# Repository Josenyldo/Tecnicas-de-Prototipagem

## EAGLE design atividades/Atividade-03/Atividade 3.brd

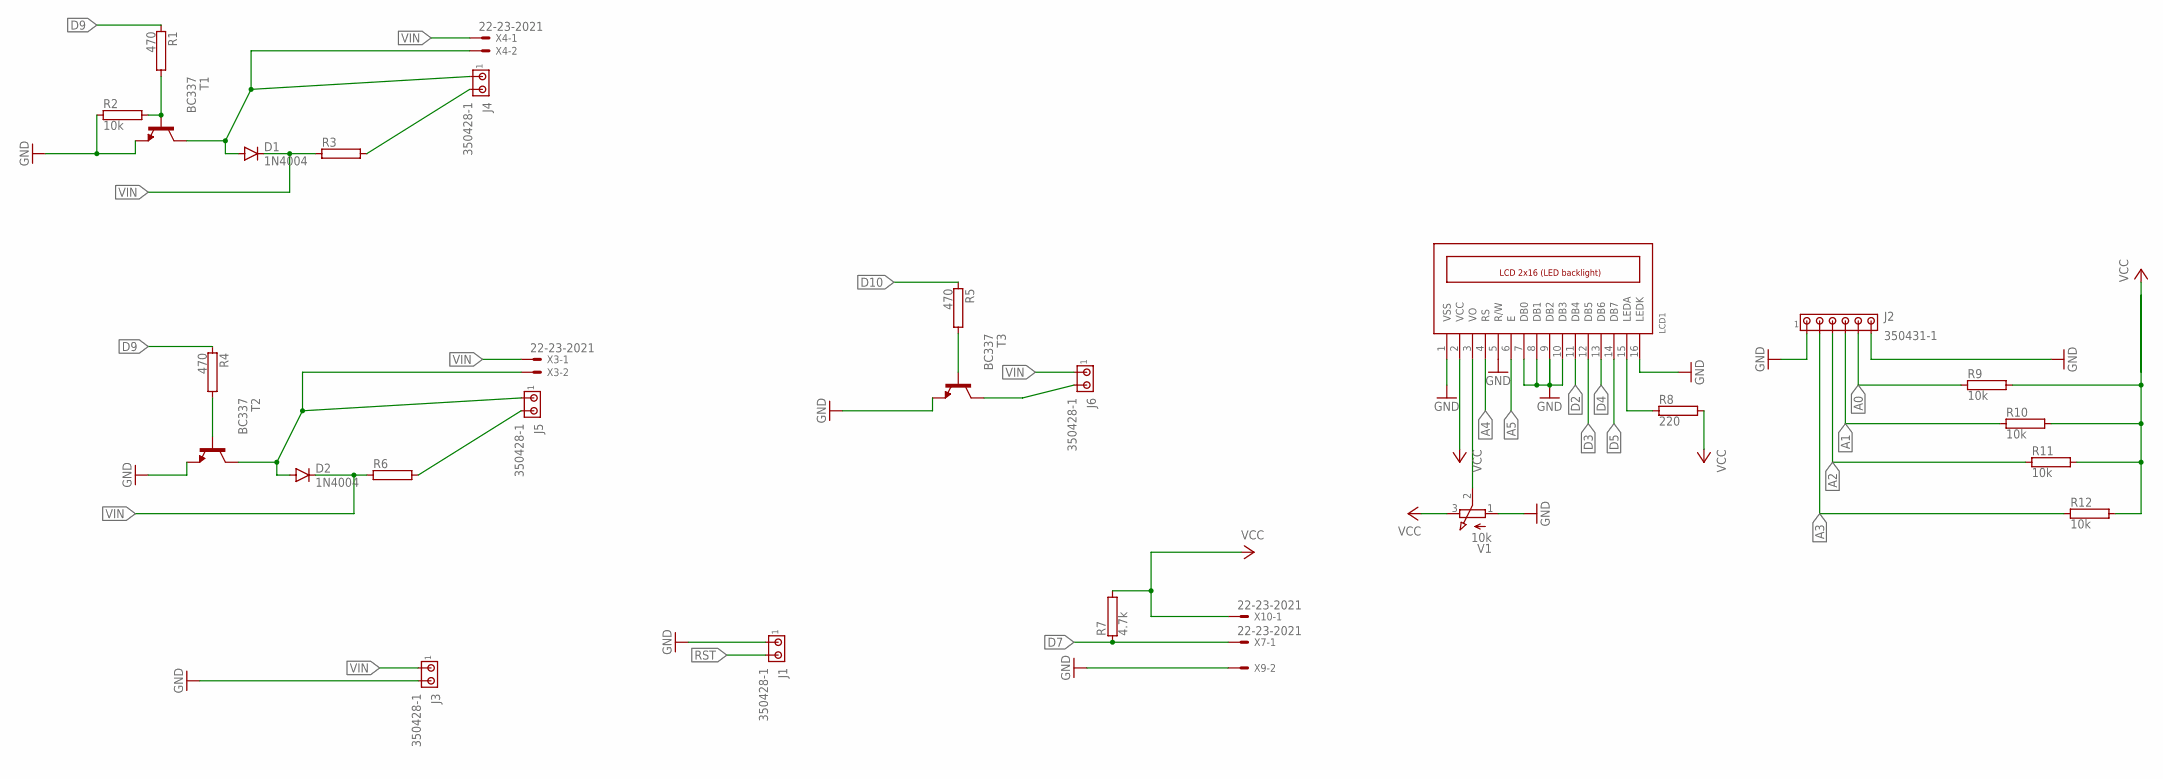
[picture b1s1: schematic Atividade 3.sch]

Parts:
D1, D2: 1N4004; DO41-10
J1, J3, J4, J5, J6: 350428-1
J2: 350431-1
LCD1: LCD_2X16_SIL; HY-1602F
R1, R4, R5: 470; AC03
R2, R9, R10, R11, R12: 10k; AC03
R3, R6: RAC03; AC03
R7: 4.7k; AC03
R8: 220; AC03
T1, T2, T3: BC337; TO92
V1: 10k; 3RP/1610N
X3, X4, X7, X9, X10: 22-23-2021

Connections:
A0: J2.5, R9.1
A1: J2.4, R10.1
A2: J2.3, R11.1
A3: J2.2, R12.1
A4: LCD1.4 (RS)
A5: LCD1.6 (E)
D1: LCD1.2 (VCC), R7.2, R8.2, V1.3 (E), X10.1
D2: LCD1.11 (DB4)
D3: LCD1.12 (DB5)
D4: LCD1.13 (DB6)
D5: LCD1.14 (DB7)
D7: R7.1, X7.1
D9: R1.1, R4.1
D10: R5.1
GND: J1.1, J2.1, J2.6, J3.2, LCD1.1 (VSS), R2.1, T1.1 (E), T2.1 (E), T3.1 (E), V1.1 (A), X9.2
unnamed: R1.2, R2.2, T1.2 (B)
unnamed: J4.2, R3.2
unnamed: R4.2, T2.2 (B)
unnamed: R5.2, T3.2 (B)
unnamed: J5.2, R6.2
unnamed: LCD1.3 (VO), V1.2 (S)
unnamed: LCD1.7 (DB0), LCD1.8 (DB1), LCD1.9 (DB2), LCD1.10 (DB3)
unnamed: LCD1.15 (LEDA), R8.1
unnamed: R9.2, R10.2, R11.2, R12.2
RST: J1.2
VIN: D1.A, D1.C, D2.A, D2.C, J3.1, J4.1, J5.1, J6.1, J6.2, R3.1, R6.1, T1.3 (C), T2.3 (C), T3.3 (C), X3.1, X3.2, X4.1, X4.2

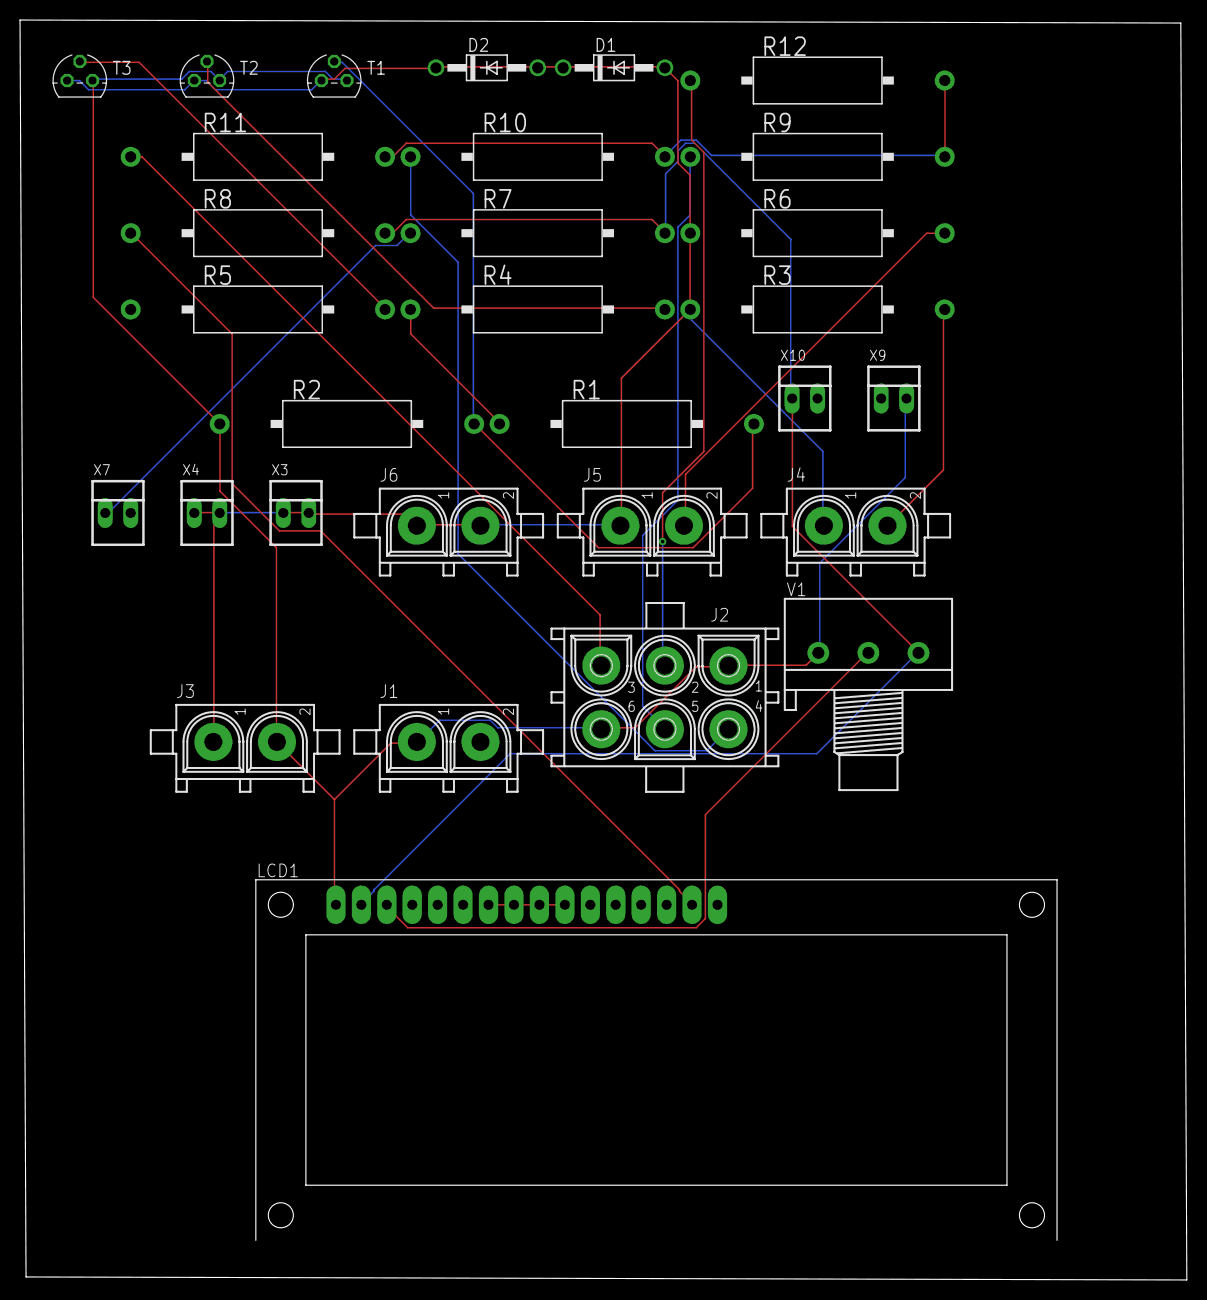
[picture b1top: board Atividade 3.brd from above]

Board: 2 copper layers, 116.5 x 125.8 mm, 30 parts (0 on the bottom side), 18 nets.

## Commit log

2021-12-05 Segunda Atividade
    Diagrama esquemático.
2022-03-27 Terceira atividade
